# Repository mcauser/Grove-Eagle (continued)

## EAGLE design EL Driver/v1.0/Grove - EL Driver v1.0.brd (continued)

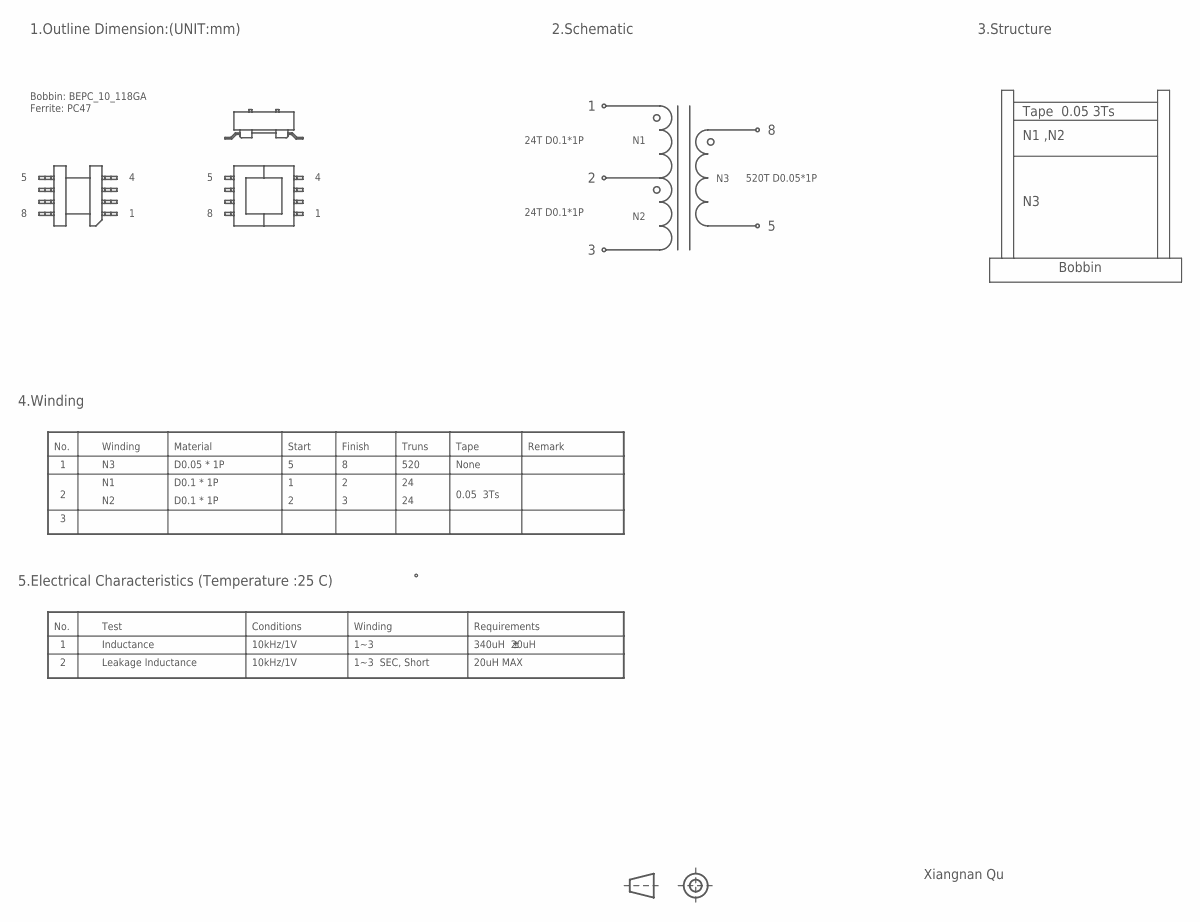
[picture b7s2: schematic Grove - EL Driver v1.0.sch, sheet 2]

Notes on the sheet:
Bobbin: BEPC_10_118GA
1.Outline Dimension:(UNIT:mm)
Ferrite: PC47
2.Schematic
Tape 0.05 3Ts
Start
Finish
Truns
Material
Winding
No.
D0.1 * 1P
520
D0.05 * 1P
N1 ,N2
3.Structure
4.Winding
Tape
Remark
None
0.05 3Ts
5.Electrical Characteristics (Temperature :25 C)
Conditions
Test
Leakage Inductance
10kHz/1V
1~3
Inductance
Requirements
1~3 SEC, Short
340uH 20uH
20uH MAX
24T D0.1*1P
520T D0.05*1P
Xiangnan Qu
Bobbin

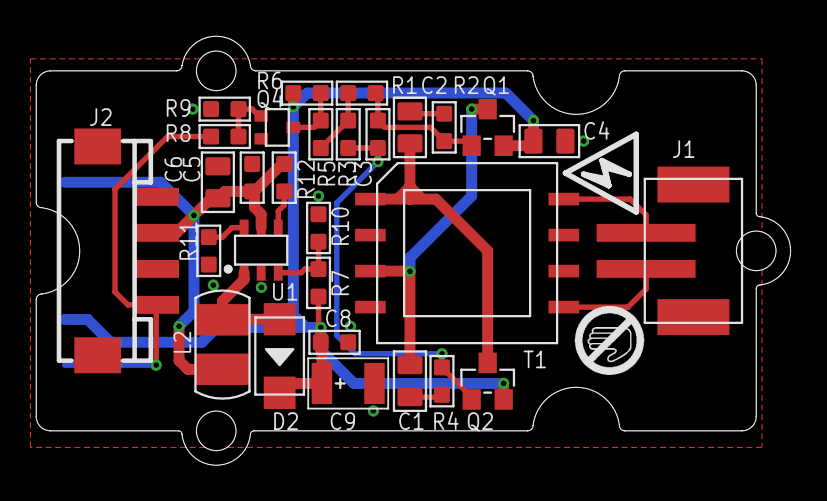
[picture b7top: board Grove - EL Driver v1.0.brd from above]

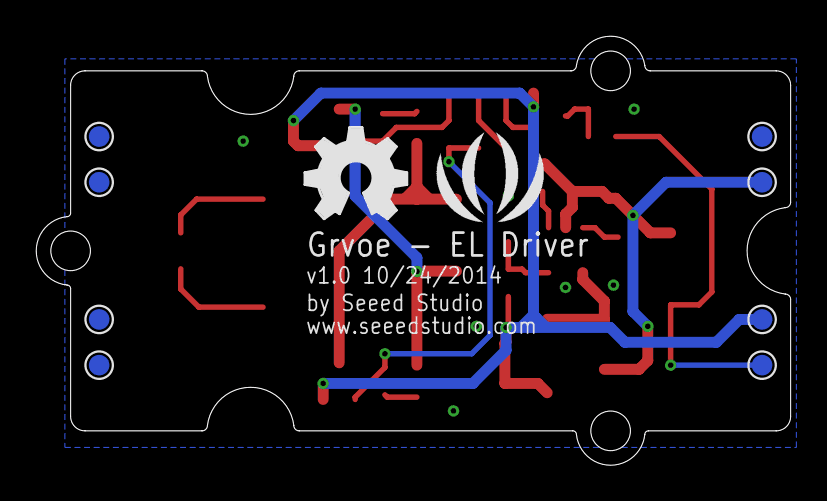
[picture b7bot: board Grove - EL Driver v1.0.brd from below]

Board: 2 copper layers, 41.9 x 23.8 mm, 40 parts (10 on the bottom side), 19 nets.

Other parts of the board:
U$2: GROVE-1*2-TEST-PLATFORM
U$4: OSHW_FILLX200_NOTEXT
U$8: SEEED-SILK-280*268MIL
